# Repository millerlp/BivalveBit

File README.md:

# BivalveBit

A custom data logger designed to monitor bivalve mollusc heart rate, valve
gape, and external temperature. Designed to be housed in a 3/4" schedule 40 
PVC plumbing pipe along with an 18650-size Lithium-Ion battery cell. 

Current hardware revision E (Fall 2021). See the Hardware folder for KiCad
design files.

Programmed in the Arduino environment.
 
Requires the separate BivalveBit_lib library available at: 
https://github.com/millerlp/BivalveBit_lib

 Based on ATmega4808 MCU using MegaCoreX board definition
 https://github.com/MCUdude/MegaCoreX

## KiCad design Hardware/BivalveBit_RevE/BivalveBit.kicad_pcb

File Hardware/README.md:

# BivalveBit hardware
 Heart rate and valve gape sensor wearable for oysters and mussels. 
 
 * Based around a ATmega4808 microcontroller
 * Designed to fit inside a nominal 3/4" schedule 40 PVC plumbing pipe (<18.5mm
 inside diameter) along with an 18650 size Lithium-Ion battery cell. 
 * Provides one I2C 4-pin port for communicating with a IR heart rate sensor
 * Provides one analog 4-pin port for communicating with an analog sensor such
 as the A1395 Hall effect sensor (with SLEEP pin on the 4th wire). 
 * Writes data to a standard microSD card
 
 Hardware design files for the main board were originally created in KiCad 5.1, 
 in the directory BivalveBit_RevE. The files have been updated to KiCad 6.0.1. 
 
 Hardware design files for the heart rate (and temperature) sensor board
 were created in Autodesk EAGLE 9.6, and are available in the 
 Mussel_heartrate_RevC_EAGLE directory. A version imported into KiCad 6.0.1 is available
 in the directory Mussel_heartrate_RevC_KiCad. 
 
 Hardware design files in KiCad 6.0.1 for the Hall effect sensor board using an Allegro A1395
 Hall effect sensor can be found in the directory Hall_effect_sensor_board_A139x.

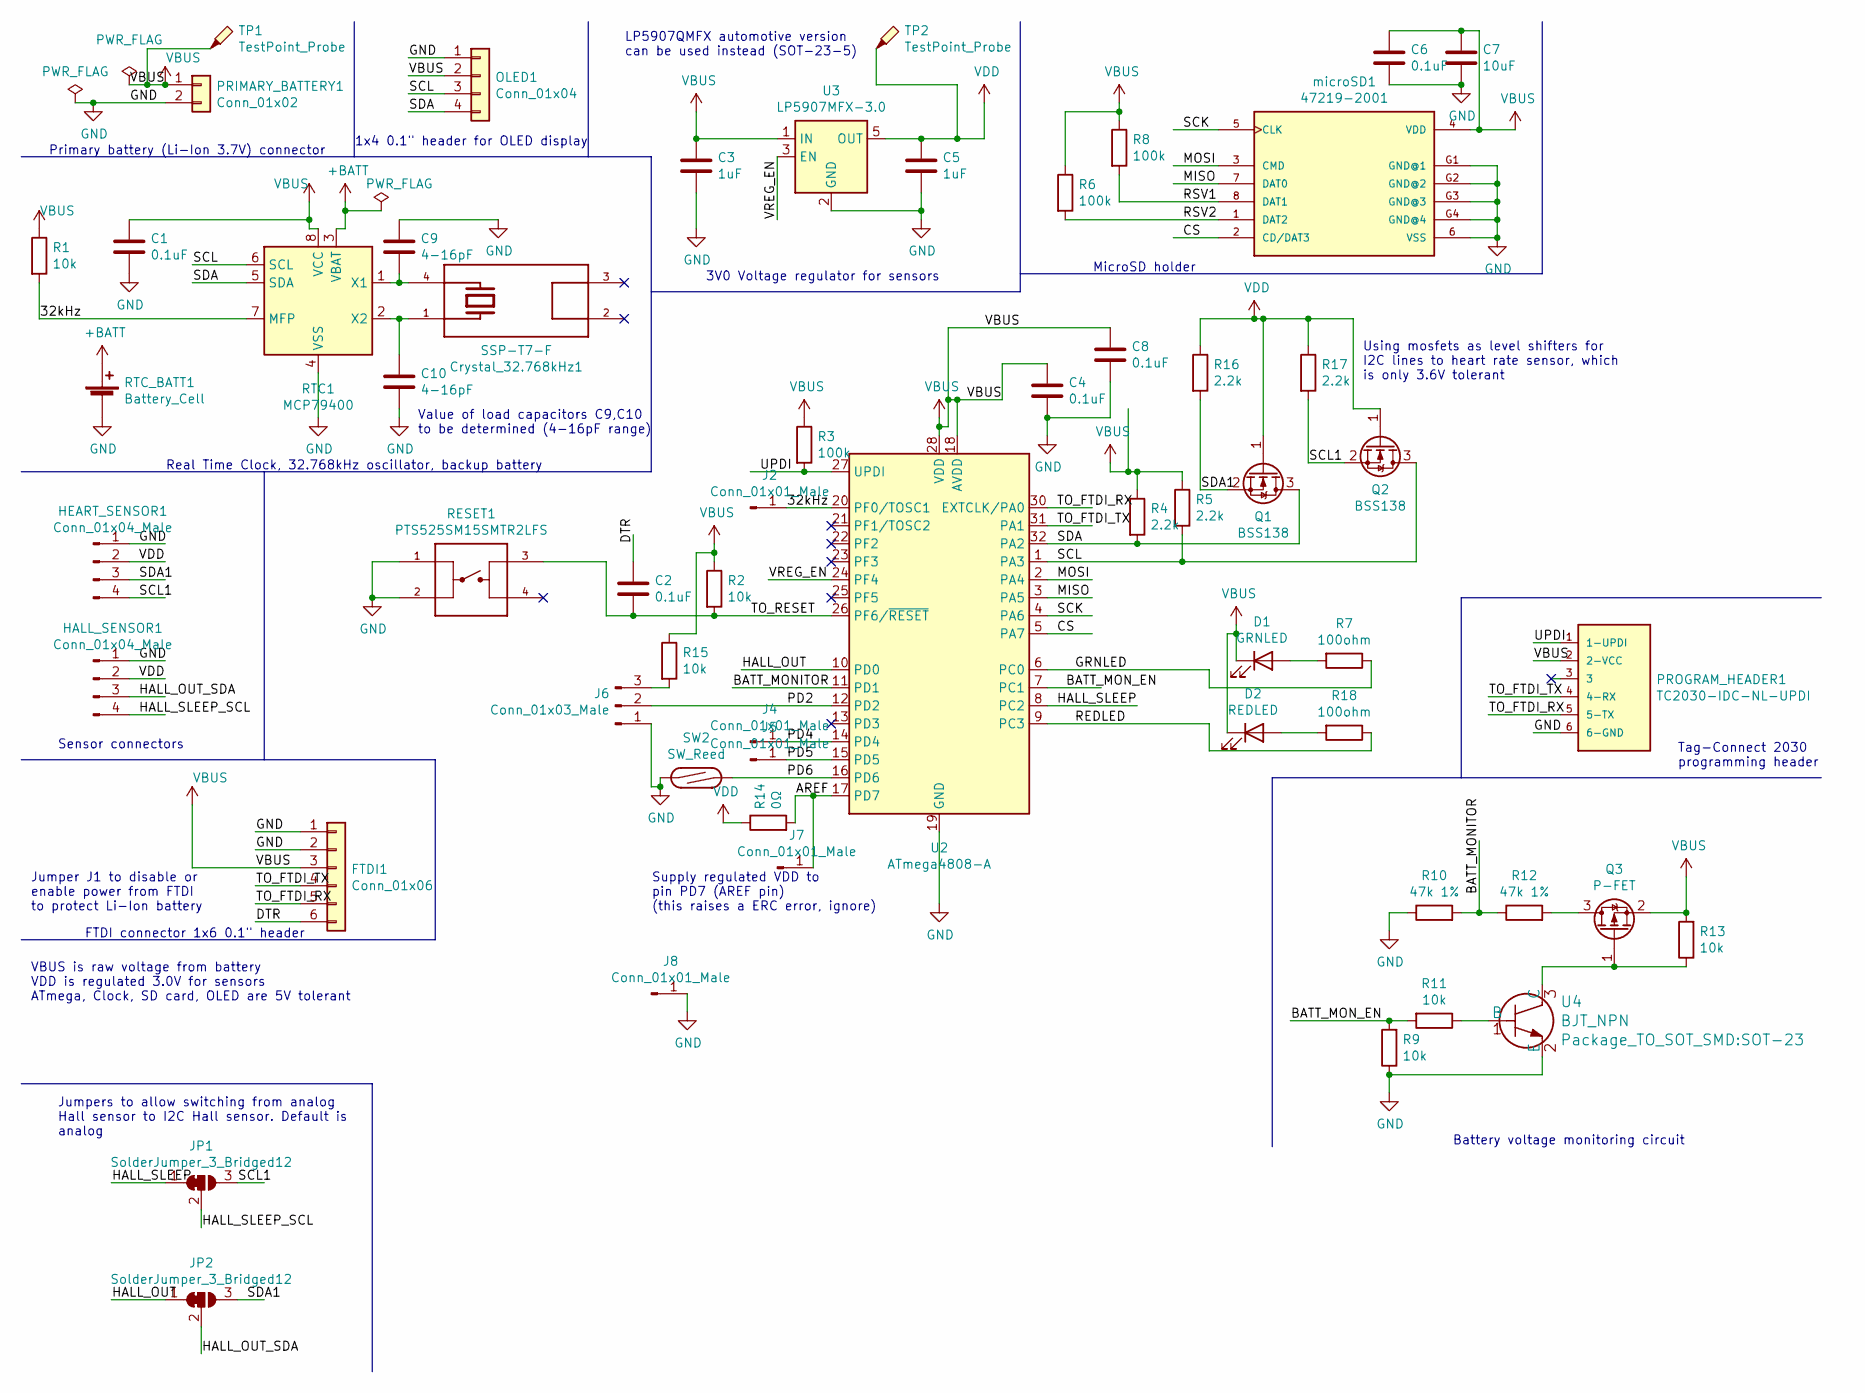
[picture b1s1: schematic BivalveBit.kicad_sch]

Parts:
C1, C2, C4, C6, C8: 0.1uF; C_0603_1608Metric
C3, C5: 1uF; C_0603_1608Metric
C7: 10uF; C_0603_1608Metric
C9, C10: 4-16pF; C_0603_1608Metric
Crystal_32.768kHz1: SSP-T7-F; OSC_SSP-T7-F; PARTREV N/A
D1: GRNLED; LED_0805_2012Metric
D2: REDLED; LED_0805_2012Metric
FTDI1: Conn_01x06; PinSocket_1x06_P2.54mm_Horizontal
HALL_SENSOR1: Conn_01x04_Male; JST_PH_B4B-PH-K_1x04_P2.00mm_Vertical
HEART_SENSOR1: Conn_01x04_Male; JST_PH_B4B-PH-K_1x04_P2.00mm_Vertical
J2, J4, J5, J7, J8: Conn_01x01_Male; Pin_D1.0mm_L10.0mm
J6: Conn_01x03_Male; PinHeader_1x03_P2.54mm_Vertical
JP1, JP2: SolderJumper_3_Bridged12; SolderJumper-3_P1.3mm_Bridged12_RoundedPad1.0x1.5mm
OLED1: Conn_01x04; PinHeader_1x04_P2.54mm_Vertical
PRIMARY_BATTERY1: Conn_01x02; JST_PH_B2B-PH-K_1x02_P2.00mm_Vertical
PROGRAM_HEADER1: TC2030-IDC-NL-UPDI; Tag-Connect_TC2030-IDC-NL_2x03_P1.27mm_Vertical; PARTREV MS
Q1, Q2: BSS138; SOT-23
Q3: P-FET; SOT-23
R1, R2, R9, R11, R13, R15: 10k; R_0603_1608Metric
R3, R6, R8: 100k; R_0603_1608Metric
R4, R5, R16, R17: 2.2k; R_0603_1608Metric
R7, R18: 100ohm; R_0603_1608Metric
R10, R12: 47k 1%; R_0603_1608Metric
R14: 0Ω; R_0603_1608Metric
RESET1: PTS525SM15SMTR2LFS; SW_PTS525SM15SMTR2LFS; PARTREV NA
RTC1: MCP79400; MSOP-8_3x3mm_P0.65mm
RTC_BATT1: Battery_Cell; BatteryHolder_Keystone_3000_1x12mm
SW2: SW_Reed; SW_SPST_REED_CT10-XXXX-G1
TP1, TP2: TestPoint_Probe; TestPoint_THTPad_D1.0mm_Drill0.5mm
U2: ATmega4808-A; TQFP-32_7x7mm_P0.8mm
U3: LP5907MFX-3.0; SOT-23-5
U4: BJT_NPN; SOT-23
microSD1: 47219-2001; MOLEX_47219-2001; Digikey WM6698CT-ND

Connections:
+BATT: RTC1.3 (VBAT), RTC_BATT1.1 (+)
/32kHz: J2.1, R1.2, RTC1.7 (MFP), U2.20 (PF0/TOSC1)
/AREF: J7.1, R14.2, U2.17 (PD7)
/BATT_MONITOR: R10.2, R12.1, U2.11 (PD1)
/BATT_MON_EN: R9.2, R11.2, U2.7 (PC1)
/CS: U2.5 (PA7), microSD1.2 (CD/DAT3)
/DTR: C2.1, FTDI1.6
/GRNLED: R7.1, U2.6 (PC0)
/HALL_OUT: JP2.1 (A), U2.10 (PD0)
/HALL_OUT_SDA: HALL_SENSOR1.3, JP2.2 (C)
/HALL_SLEEP: JP1.1 (A), U2.8 (PC2)
/HALL_SLEEP_SCL: HALL_SENSOR1.4, JP1.2 (C)
/MISO: U2.3 (PA5), microSD1.7 (DAT0)
/MOSI: U2.2 (PA4), microSD1.3 (CMD)
/PD2: J6.2, U2.12 (PD2)
/PD4: J4.1, U2.14 (PD4)
/PD5: J5.1, U2.15 (PD5)
/PD6: SW2.2, U2.16 (PD6)
/REDLED: R18.1, U2.9 (PC3)
/RSV1: R8.2, microSD1.8 (DAT1)
/RSV2: R6.2, microSD1.1 (DAT2)
/SCK: U2.4 (PA6), microSD1.5 (CLK)
/SCL: OLED1.3, Q2.3 (D), R5.2, RTC1.6 (SCL), U2.1 (PA3)
/SCL1: HEART_SENSOR1.4, JP1.3 (B), Q2.2 (S), R17.2
/SDA: OLED1.4, Q1.3 (D), R4.2, RTC1.5 (SDA), U2.32 (PA2)
/SDA1: HEART_SENSOR1.3, JP2.3 (B), Q1.2 (S), R16.2
/TO_FTDI_RX: FTDI1.5, PROGRAM_HEADER1.5 (5-TX), U2.30 (EXTCLK/PA0)
/TO_FTDI_TX: FTDI1.4, PROGRAM_HEADER1.4 (4-RX), U2.31 (PA1)
/TO_RESET: C2.2, R2.2, RESET1.3, U2.26 (PF6/~RESET)
/UPDI: PROGRAM_HEADER1.1 (1-UPDI), R3.2, U2.27 (UPDI)
/VREG_EN: U2.24 (PF4), U3.3 (EN)
GND: C1.2, C3.2, C4.2, C5.2, C6.2, C7.2, C8.2, C9.1, C10.2, FTDI1.1, FTDI1.2, HALL_SENSOR1.1, HEART_SENSOR1.1, J6.1, J8.1, OLED1.1, PRIMARY_BATTERY1.2, PROGRAM_HEADER1.6 (6-GND), R9.1, R10.1, RESET1.1, RESET1.2, RTC1.4 (VSS), RTC_BATT1.2 (-), SW2.1, U2.19 (GND), U2.29 (GND), U3.2 (GND), U4.2 (E), microSD1.6 (VSS), microSD1.G1 (GND@1), microSD1.G2 (GND@2), microSD1.G3 (GND@3), microSD1.G4 (GND@4)
unnamed: C9.2, Crystal_32.768kHz1.4, RTC1.1 (X1)
unnamed: C10.1, Crystal_32.768kHz1.1, RTC1.2 (X2)
unnamed: D1.2 (A), R7.2
unnamed: D2.2 (A), R18.2
unnamed: J6.3, R15.2
unnamed: Q3.1 (G), R13.1, U4.3 (C)
unnamed: Q3.3 (D), R12.2
unnamed: R11.1, U4.1 (B)
VBUS: C1.1, C3.1, C4.1, C6.1, C7.1, C8.1, D1.1 (K), D2.1 (K), FTDI1.3, OLED1.2, PRIMARY_BATTERY1.1, PROGRAM_HEADER1.2 (2-VCC), Q3.2 (S), R1.1, R2.1, R3.1, R4.1, R5.1, R6.1, R8.1, R13.2, R15.1, RTC1.8 (VCC), TP1.1, U2.18 (AVDD), U2.28 (VDD), U3.1 (IN), microSD1.4 (VDD)
VDD: C5.1, HALL_SENSOR1.2, HEART_SENSOR1.2, Q1.1 (G), Q2.1 (G), R14.1, R16.1, R17.1, TP2.1, U3.5 (OUT)

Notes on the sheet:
Primary battery (Li-Ion 3.7V) connector
Battery voltage monitoring circuit
Using mosfets as level shifters for I2C lines to heart rate sensor, which is only 3.6V tolerant
Jumpers to allow switching from analog Hall sensor to I2C Hall sensor. Default is analog
FTDI connector 1x6 0.1" header
Sensor connectors
1x4 0.1" header for OLED display
Real Time Clock, 32.768kHz oscillator, backup battery
Supply regulated VDD to pin PD7 (AREF pin) (this raises a ERC error, ignore)
Value of load capacitors C9,C10 to be determined (4-16pF range)
LP5907QMFX automotive version can be used instead (SOT-23-5)
Jumper J1 to disable or enable power from FTDI to protect Li-Ion battery
3V0 Voltage regulator for sensors
VBUS is raw voltage from battery VDD is regulated 3.0V for sensors ATmega, Clock, SD card, OLED are 5V tolerant
MicroSD holder
Tag-Connect 2030 programming header

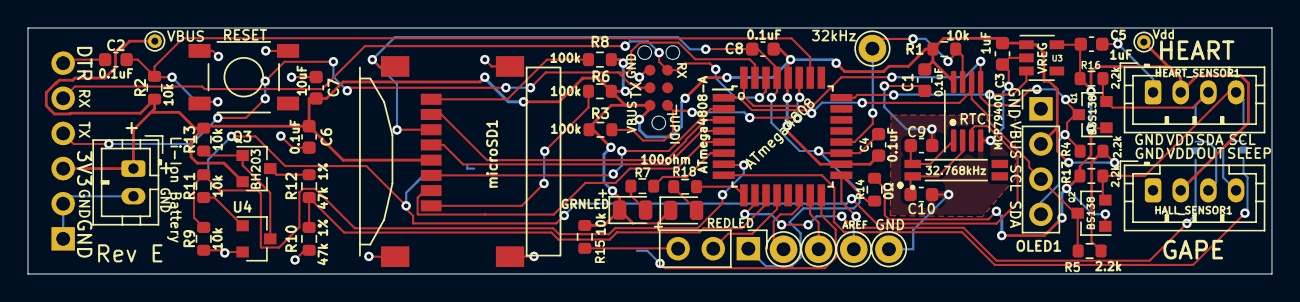
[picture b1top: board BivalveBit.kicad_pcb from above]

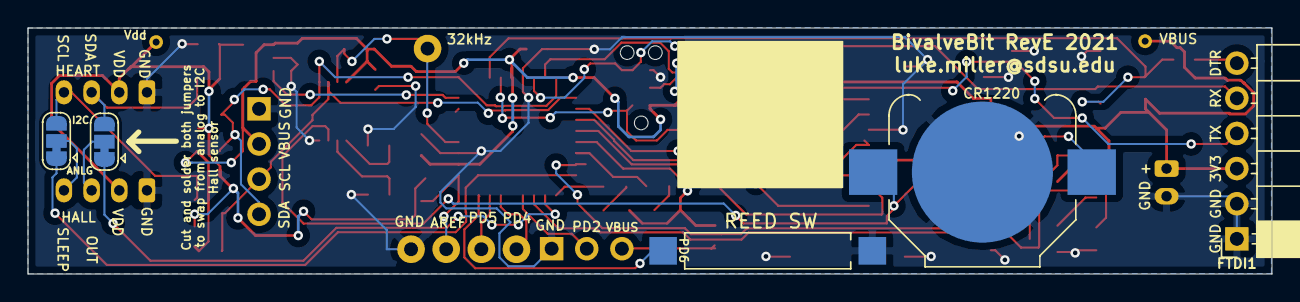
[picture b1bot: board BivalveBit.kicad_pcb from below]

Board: 2 copper layers, 89.9 x 17.8 mm, 58 parts (5 on the bottom side), 42 nets.

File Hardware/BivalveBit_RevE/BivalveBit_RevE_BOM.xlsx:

| BivalveBit Rev E 2021-09
Id | Designator | Package | Quantity | Designation | Supplier and ref
2 | RTC_BATT1 | BatteryHolder_Keystone_3000_1x12mm | 1 | Battery_Cell
4 | HEART_SENSOR1,HALL_SENSOR1 | JST_PH_B4B-PH-K_1x04_P2.00mm_Vertical | 2 | Conn_01x04_Male | JST PH 4-pin
5 | R17,R16,R5,R4 | R_0603_1608Metric | 4 | 2.2k
6 | U4 | SOT-23 | 1 | BJT_NPN | FMMT619A, MMBT2484LT3G
7 | U3 | SOT-23-5 | 1 | LP5907MFX-3.0 | Voltage regulator
8 | U2 | TQFP-32_7x7mm_P0.8mm | 1 | ATmega4808-A | microcontroller 32-pin
9 | SW2 | SW_SPST_REED_CT10-XXXX-G1 | 1 | SW_Reed | Reed switch
10 | RESET1 | SW_PTS525SM15SMTR2LFS | 1 | PTS525SM15SMTR2LFS | tactile switch
11 | R15,R13,R11,R9,R2,R1 | R_0603_1608Metric | 6 | 10k
12 | R14 | R_0603_1608Metric | 1 | 0 ohm
13 | R12,R10 | R_0603_1608Metric | 2 | 47k 1%
14 | R8,R6,R3 | R_0603_1608Metric | 3 | 100k
15 | R7,R18 | R_0603_1608Metric | 2 | 100ohm
16 | Q3 | SOT-23 | 1 | P-FET | IRLM5203, SSM3J328R,LF
17 | Q2,Q1 | SOT-23 | 2 | BSS138 | BS138, DMB2302U-7, SSM3K329R,LF
19 | PRIMARY_BATTERY1 | JST_PH_B2B-PH-K_1x02_P2.00mm_Vertical | 1 | Conn_01x02 | JST PH 2-pin
20 | OLED1 | PinHeader_1x04_P2.54mm_Vertical | 1 | Conn_01x04 | OLED header
21 | microSD1 | MOLEX_47219-2001 | 1 | 47219-2001 | Micro SD slot
24 | FTDI1 | PinSocket_1x06_P2.54mm_Horizontal | 1 | Conn_01x06 | FTDI header
25 | D1 | LED_0805_2012Metric | 1 | GRNLED | Green LED
26 | Crystal_32.768kHz1 | OSC_SSP-T7-F | 1 | SSP-T7-F | Crystal
27 | C8,C6,C4,C2,C1 | C_0603_1608Metric | 5 | 0.1uF
28 | C7 | C_0603_1608Metric | 1 | 10uF
29 | C5,C3 | C_0603_1608Metric | 2 | 1uF
30 | C9,C10 | C_0603_1608Metric | 2 | 4-16pF
31 | RTC1 | MSOP-8_3x3mm_P0.65mm | 1 | MCP79400 | RTC
32 | D2 | LED_0805_2012Metric | 1 | REDLED | Red LED

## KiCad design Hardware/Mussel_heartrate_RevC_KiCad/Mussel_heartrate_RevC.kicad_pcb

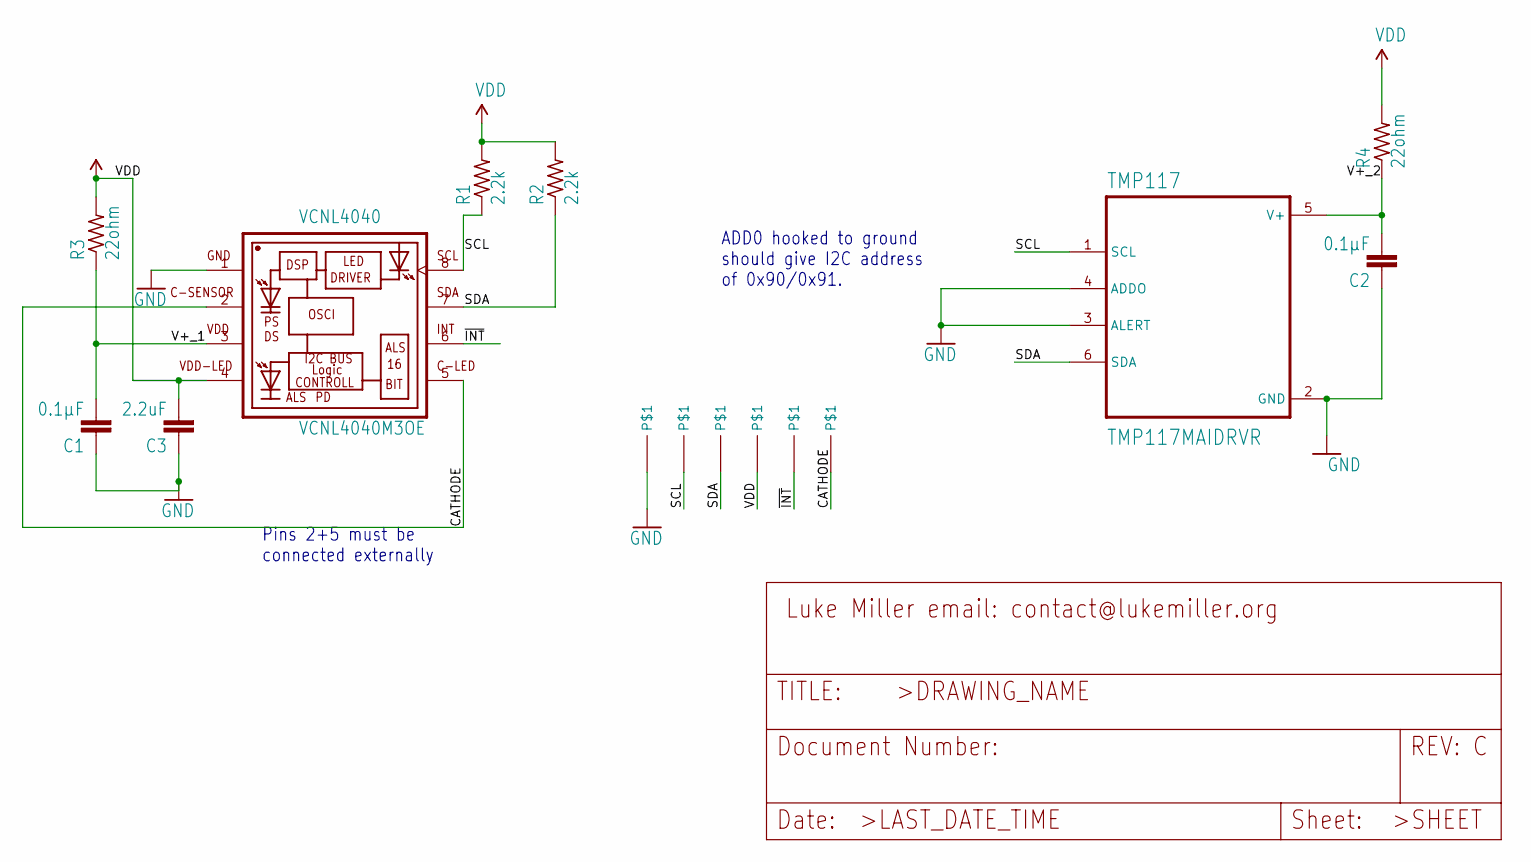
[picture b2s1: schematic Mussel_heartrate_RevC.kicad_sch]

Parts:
/~{INT}1: PINHD-1X10.7MM_DRILL; 1X01_SMALL_0.7
C1, C2: 0.1µF; C0402
C3: 2.2uF; C0402
CATHODE1: PINHD-1X10.7MM_DRILL; 1X01_SMALL_0.7
GND1: PINHD-1X1SMALL; 1X01_SMALL_HEADER_PIN_D0.9MM_W1.4MM
R1, R2: 2.2k; R0402
R3, R4: 22ohm; R0402
SCL1: PINHD-1X1SMALL; 1X01_SMALL_HEADER_PIN_D0.9MM_W1.4MM
SDA1: PINHD-1X1SMALL; 1X01_SMALL_HEADER_PIN_D0.9MM_W1.4MM
TMP117: TMP117MAIDRVR; SON65P200X200X80-7N
VCNL4040: VCNL4040M3OE; VISHAY_VCNL4040_4X2X1.1
VDD1: PINHD-1X1SMALL; 1X01_SMALL_HEADER_PIN_D0.9MM_W1.4MM

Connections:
/CATHODE: CATHODE1.P$1, VCNL4040.2 (C-SENSOR), VCNL4040.5 (C-LED)
/SCL: R1.1, SCL1.1, TMP117.1 (SCL), VCNL4040.8 (SCL)
/SDA: R2.1, SDA1.1, TMP117.6 (SDA), VCNL4040.7 (SDA)
/V+_1: C1.2, R3.1, VCNL4040.3 (VDD)
/V+_2: C2.2, R4.1, TMP117.5 (V+)
/~INT: /~{INT}1.P$1, VCNL4040.6 (INT)
GND: C1.1, C2.1, C3.1, GND1.1, TMP117.2 (GND), TMP117.3 (ALERT), TMP117.4 (ADDO), VCNL4040.1 (GND)
VCC: C3.2, R1.2, R2.2, R3.2, R4.2, VCNL4040.4 (VDD-LED), VDD1.1

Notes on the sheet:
ADD0 hooked to ground should give I2C address of 0x90/0x91.
Pins 2+5 must be connected externally

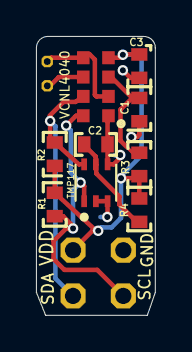
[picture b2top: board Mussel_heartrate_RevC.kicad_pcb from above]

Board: 2 copper layers, 6.6 x 15.5 mm, 15 parts (0 on the bottom side), 8 nets.

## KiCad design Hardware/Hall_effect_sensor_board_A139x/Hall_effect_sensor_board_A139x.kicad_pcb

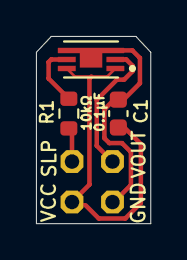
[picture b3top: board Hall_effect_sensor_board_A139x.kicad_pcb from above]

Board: 2 copper layers, 6.4 x 10.4 mm, 4 parts (0 on the bottom side), 5 nets.

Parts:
C1: 0.1µF; C_0603_1608Metric
HALL1_HEADER1: PINHD-2X21.5MM_SILK; 2X2_2.25MM
R1: 10kΩ; R_0603_1608Metric
U1: A1395SEHLT-T; SENSOR_A1395SEHLT-T

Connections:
/HALL1_GND: C1.2, HALL1_HEADER1.P$1 (1), U1.3 (GND), U1.4 (GND)
/HALL1_VCC: C1.1, HALL1_HEADER1.P$2 (2), U1.1 (VCC), U1.6 (VREF)
/HALL1_VOUT: HALL1_HEADER1.P$3 (3), U1.2 (OUT)
/HALL1_~SLEEP_IN: HALL1_HEADER1.P$4 (4), R1.1
/~SLEEP1: R1.2, U1.5 (~SLEEP)

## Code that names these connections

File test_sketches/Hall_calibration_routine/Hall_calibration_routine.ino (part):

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 *  If you don't have a Model 200 syringe dispenser sitting around,
 *  don't bother running this program.
 *  
 *  Connect Syringe Trigger pin to MusselTracker pin PD2
 *  Connect Syringe GND to MusselTracker GND
 *  On the KD200 dispenser, set the syringe DIA to 50.00mm
 *  Set the Vol to 0.623ml
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 * Hall effect sensor definitions
 ************************************************************/
#define ANALOG_IN A0  // Analog input pin for Hall sensor
#define HALL_SLEEP 10 // Hall sensor sleep pin, pull high to wake
unsigned int HallValue = 0; // Variable for Hall sensor reading

/***************************************************************************************************
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//------------------------------------------------------------
//  Battery monitor 
#define BATT_MONITOR_EN  9 // digital output channel to turn on battery voltage check
#define BATT_MONITOR  A1  // analog input channel to sense battery voltage
float dividerRatio = 2; // Ratio of voltage divider (47k + 47k) / 47k = 2
float refVoltage = 3.00; // Voltage at AREF pin on ATmega microcontroller, measured per board
float batteryVolts = 0; // Estimated battery voltage returned from readBatteryVoltage function
float minimumVoltage = 3.4; // Minimum safe voltage for a Li-Ion battery
unsigned int lowVoltageCount = 0; // Count how many times voltage is too low
unsigned int lowVoltageCountLimit = 10; // Number of loops after which the program should be shutdown
#define REDLED 11   // Red LED pin
#define GRNLED 8    // Green LED pin
#define VREG_EN 24  // voltage regulator enable
#define TRIGGER 14 // External trigger to syringe pump, PD2 pin, Arduino pin 14(A2)


void test_pin_init(void){
    /* Make High (OFF) */
    PORTC.OUT |= PIN0_bm; // BivalveBit green led on pin PC0 (arduino pin 8)
    /* Make output */
    PORTC.DIR |= PIN0_bm;

    /* Make High (OFF) */
    PORTC.OUT |= PIN3_bm; // BivalveBit red led on pin PC3 (arduino pin 11)
    /* Make output */
    PORTC.DIR |= PIN3_bm;
    
    /* Make High (OFF) */
    PORTD.OUT |= PIN2_bm; // Pin PD2 (probe with scope/analyzer) - used to activate syringe pump
    /* Make output */
    PORTD.DIR |= PIN2_bm;
}
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{
    /* You must clear PIT interrupt flag by writing '1': */
    RTC.PITINTFLAGS = RTC_PI_bm;
//    PORTD.OUTTGL |= PIN2_bm; // Toggle PD2 (probe with scope/analyzer)
//    PORTC.OUTTGL |= PIN0_bm; // BivalveBit green led on pin PC0 
}


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  analogReference(EXTERNAL);
  setUnusedPins(); // in BivalveBit_lib
  disableUnusedPeripherals(); // in BivalveBit_lib
  pinMode(VREG_EN, OUTPUT);   // Voltage regulator pin
  digitalWrite(VREG_EN, LOW); // set low to turn off, high to turn on (~150usec to wake)
  pinMode(20, INPUT_PULLUP); // pin PF0, attached to RTC multi-function pin
  // Battery monitor pins
  pinMode(BATT_MONITOR, INPUT); // Battery voltage input channel
  pinMode(BATT_MONITOR_EN, OUTPUT); // Battery monitor enable pin
  digitalWrite(BATT_MONITOR_EN, LOW); // pull low to turn off battery monitor circuit
  test_pin_init(); // Set up the LEDs and PD2 output pin
  //---------------------------------
  // Retrieve board serial number
  EEPROM.get(0, serialNumber);
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
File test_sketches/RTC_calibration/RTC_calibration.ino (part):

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int8_t trimValue = 0; // Signed crystal frequency trimming value -127 to +127
long oldticks = 0;

#define GPSinput 14 // Take input on PD2, digital pin 14
#define GRNLED 8 

#define RTC_EXAMPLE_PERIOD (32767) // Set how high the RTC will run before overflow (max 32767)

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
  Wire.begin();
  pinMode(GPSinput, INPUT);
  pinMode(GRNLED, OUTPUT);
  digitalWrite(GRNLED, HIGH);
  pinMode(17, OUTPUT);  // PD5 = D17
  pinMode(16, OUTPUT);  // PD4 = D16
  Serial.println("Clock check");

  oled.begin(&Adafruit128x32, I2C_ADDRESS1);  
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    Serial.print(rtcRawCount);
    Serial.print("\t diff: ");
    Serial.println((long)rtcRawCount - oldticks);
    PORTD.IN |= PIN4_bm; // Toggle pin PD4 also
    
    oled.clear();
    oled.home();
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  {
    RTC.INTFLAGS = RTC_OVF_bm; // Clear the interrupt by writing '1' to the overflow bit in RTC.INTFLAGS
    RTCticks++; // increment RTCticks counter
    PORTC.IN |= PIN0_bm;  // Toggle pin PC0 attached to green led
    PORTD.IN |= PIN5_bm; // Toggle pin PD5 also

  }

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
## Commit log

2021-08-05 Put some info in the readme
2021-08-06 Working RTC example
    MCP79400T real time clock working
2021-08-06 adding this
2021-08-06 VCNL4040 basic test - works
2021-08-06 Tested working with 128x32 I2C display
    Purchased from Amazon: "WayinTop 3PCS 0.91 inch OLED Display Module IIC"
2021-08-06 Swap these around
2021-08-06 Tested working with RevB
    Be sure to have SdFat-beta (2.1 or later) installed
2021-08-22 Renaming test sketches
2021-08-22 Updated and working
2021-08-22 Tested working on RevB
2021-08-23 Basic working example, need to calibrate
2021-08-26 Add a link to the library
2021-08-26 Link to required libraries
2021-08-26 Basic version, several TODOs still
2021-08-27 Basic working test
2021-08-27 Renaming some files in order
2021-08-27 Sort of works with TMP117
2021-08-27 renamed
2021-08-27 Working with TMP117 sensor
2021-08-31 Renamed and removed
2021-08-31 Testing battery voltage reading
2021-09-01 Update note: Run at 8MHz, not 16MHz
2021-09-01 Fixing notes
2021-09-01 Testing different voltage references
2021-09-01 Tested working
2021-09-01 Initial setup of all peripherals
2021-09-01 Minimal working version
    For some reason some of the RevB boards were acting flaky and apparently resetting partway through the setup loop (browning out?), but in other cases they work fine.
2021-09-07 New revision
2021-09-07 Starting to add in more components
2021-09-07 Testing why the RTC doesn't start reliably
2021-09-22 Need to turn on VREG to test sensor
2021-09-22 No longer needed.
2021-09-22 Give VREG time to turn on
    Before searching for the temp sensor, make sure the VREG has powered up fully (~150 µsec)
2021-09-22 Making serial numbers, start at SN101
2021-09-22 Fix LED pin assignments, turn on VREG
2021-09-28 Building boards 103/104, with 6pF crystal caps
2021-09-29 Running at half speed on RTC?
2021-09-29 Seems to output at correct rate now
    Needed to define RTC.PER value at 32768-1 (= 32767) so that the 32.768kHz signal was causing an overflow every 32768 crystal cycles
2021-09-29 Still have a 10-tick drift on the RTC
    Maybe due to processing time?
2021-10-06 Still messing around, not great yet
2021-10-06 Moving the RTC ticks check into the GPS interrupt
2021-10-07 Fix variable type
    Need to make these signed because the RTC can run faster than GPS and result in a negative difference between the two counts.
2021-11-01 New unified test program
    Use to test newly assembled sensors
2021-11-01 Adding more messages
2021-11-01 Add 3rd digit to filename serialnumber
2021-11-01 Making new boards
2021-11-01 Fix printing sd message
2021-11-01 Testing LEDs at start
2022-01-01 Adding some comments
2022-01-01 Basic working sleep function
2022-01-01 Incomplete - working on ISR pin change
    Need to put together ISR and learn how to handle pin change interrupt correctly
2022-01-11 Working wake-from-sleep at 1Hz
2022-01-11 Nothing to see here yet
2022-01-12 Still not working
2022-01-13 Renamed and deleted
2022-01-13 Functional Periodic Interrupt Timer
2022-01-14 Testing lower powered modes
2022-01-17 Swap back to standby
2022-01-19 Working alarm pin test
2022-01-21 Starting on a main data collection version
2022-01-21 Adding 2 interrupt routines
    1 for 8Hz fast wakes, 1 for 1-minute wakeups. TODO: ensure that the 8Hz PIT disabling routine works.
    TODO: incorporate sensor sampling and SD card writing
2022-01-25 Trying to break it, still works
2022-01-25 Working test of 8Hz / 1minute timers
    Appears to swap back and forth between the 8Hz fast sampling and 1-minute interval alarms.
2022-01-26 Starting to add in more functions
    Beginning to incorporate sensor objects and getting SD card stuff going. Still need to initialize files and add code to start new files each day.
2022-01-27 Partly working - TODOs
    Need to implement the actual IR sensor reading and writing to buffer.
    Also have an issue with board going into a reset loop when on FTDI power only and no OLED screen attached, probably a voltage droop issue and lack of capacitance in the I2C bus.
2022-01-31 Using this to test settings on IR sensor
2022-01-31 TODO: fix IR sensor readout
    I'm not getting proper readout from the IR sensor right now, possibly it needs more time to awaken and integrate measurement before being read.
2022-02-01 Testing version - start battery tests
    All sensors functional, set to sample heart every other minute for 30 seconds at 8Hz.
2022-02-01 Proves that it still works
    Setting some additional parameters on the VCNL4040 and proving that it still works with rapid turn on and turn off.
2022-02-24 KiCad files
2022-02-24 Moved and renamed
2022-02-24 RevE circuit board pic
2022-02-24 Add some details
2022-02-24 Adding links and details
2022-02-28 Moving heart rate board in
2022-02-28 Explain directories
2022-03-24 Changing cutoff voltage to 3.5
2022-03-25 Changing green flash timing
    Move the green flash to only happen once a minute when the Hall effect and temperature sensor are sampled. Starting battery test at 2 minute intervals.
2022-03-30 Fix compatibility with SdFat 2.1.2
    Changed File definition to SdFile to allow this work with SdFat v2.1.2
2022-03-30 Change comments, battery cutoff voltage
2022-05-18 Adding clock setting to the main program
    You can now set the RTC in the main data logging program using the SETDATE command.
2022-05-22 Update with new picture
2022-05-30 Remove extra comma at end of each file line
    We don't need a comma after the battery voltage since it's the last value on the line.
2022-05-31 Hall effect sensor board design
2022-05-31 Heart rate module RevC in KiCad
2022-05-31 Updating hardware file commentary
2022-05-31 Updated to KiCad 6.0.1
2022-11-21 Init commit - need to rewrite this
2022-12-01 Filenaming not working yet
    Fix the initFileName function so it stops borking the year.
2022-12-02 Try this with a working board next
2022-12-02 Fixed file naming - test hardware next
2022-12-02 Return to idle after clock setting
2022-12-02 Add some comments
2022-12-02 Increase pause
2022-12-02 Increase the wait time
    Syringe pump would miss triggers if the wait time between trigger events was less than 1500 milliseconds.
2022-12-06 Notes
2023-01-05 Updated heart sensor to 200MA & 8T
2023-01-27 Images of layout
2023-05-12 Let user know VCNL4040 was found
2023-07-03 Creating code to use MAX3010x heart sensor - UNTESTED
2023-07-06 Functional test for MAX30102 - but use 5V supply
2023-07-06 Faster sampling
2023-07-10 Making this a bit more user-friendly, fail gracefully
    Should be functional for testing if the various sensors (gape sensor, VCNL4040, TMP117) and clock/SD are all functional.
2024-05-20 ignore
